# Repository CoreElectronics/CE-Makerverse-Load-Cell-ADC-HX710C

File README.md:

# Makerverse™ Load Cell ADC

This is the repo for the Core Electronics [Makerverse Load Cell ADC](https://core-electronics.com.au/catalog/product/view/sku/ce08248).

The PCB layout project requires KiCAD 6.0 or newer to view. The schematic is provided in PDF format in the Documents folder.

## License
This project is open source - please review the LICENSE.md file for further licensing information.

If you have any technical questions, or concerns about licensing, please contact technical support on the [Core Electronics forums](https://forum.core-electronics.com.au/).

*\"Makerverse\" and the Makerverse logo are trademarks of Core Electronics Pty Ltd.*

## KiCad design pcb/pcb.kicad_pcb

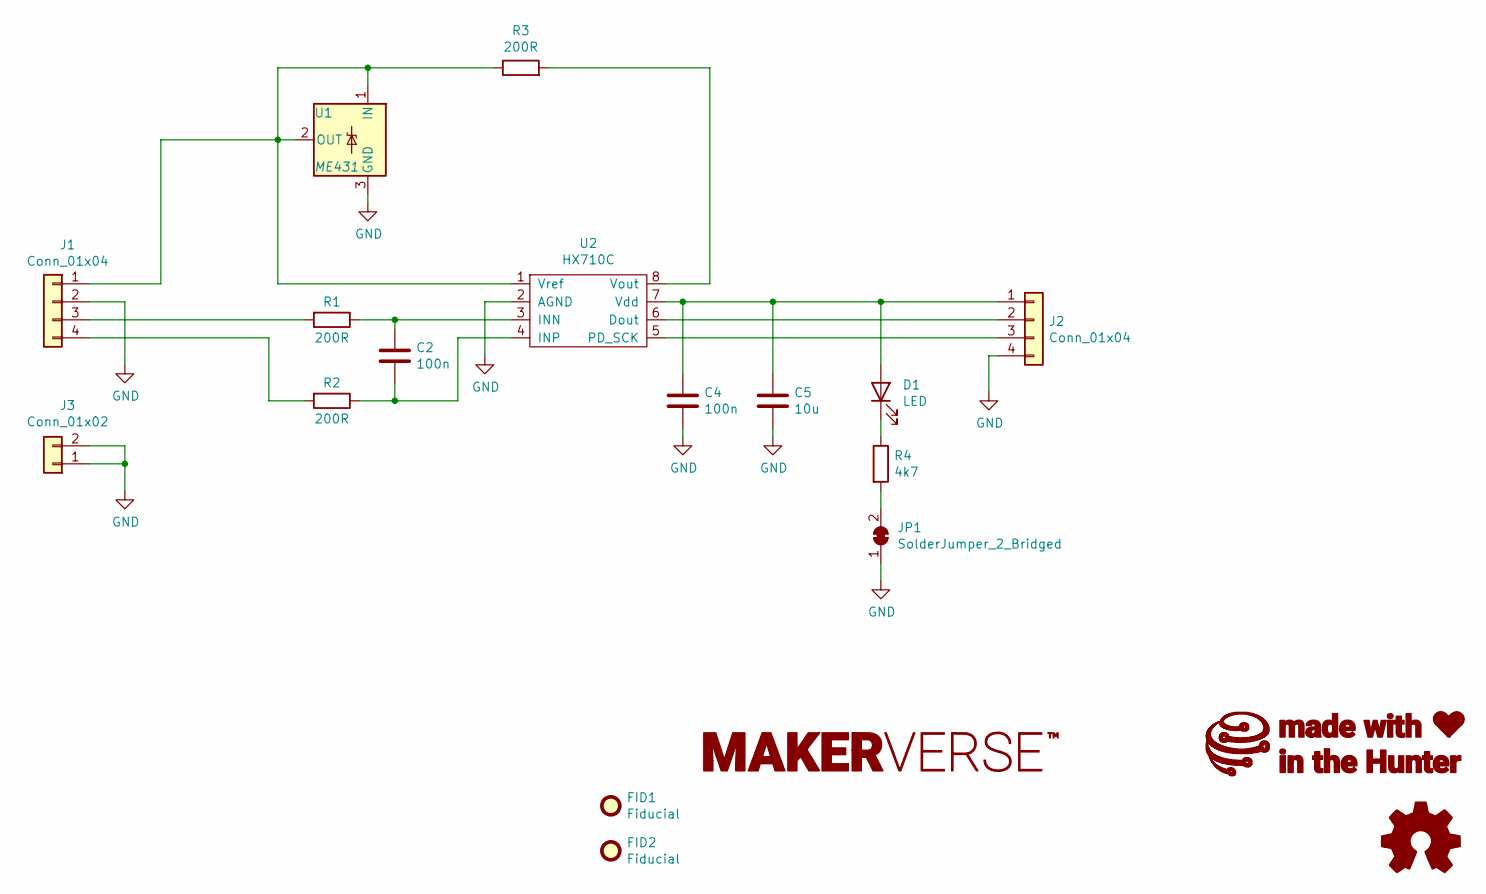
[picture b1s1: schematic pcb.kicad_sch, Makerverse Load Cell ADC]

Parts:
C2, C4: 100n; C_0402_1005Metric
C5: 10u; C_0603_1608Metric
D1: LED; LED_0603_1608Metric
FID1, FID2: Fiducial; Fiducial_1mm_Mask2mm
G1: LOGO_Makerverse; makerverse_logo_short_14.0x2.4mm
G2: LOGO_CoreElectronics_made-with-love; CE08248
J1: Conn_01x04; 2.54mm_screw_terminal-4-pin-left-entry
J2: Conn_01x04; 2.54mm_screw_terminal-4-pin-right-entry
J3: Conn_01x02; PinHeader_2x01_P2.54mm_Vertical
JP1: SolderJumper_2_Bridged; SolderJumper-2_P1.3mm_Bridged_RoundedPad1.0x1.5mm
LOGO1: Logo_Open_Hardware_Small; oshw_3.9x3.5mm
R1, R2, R3: 200R; R_0402_1005Metric
R4: 4k7; R_0402_1005Metric
U1: ME431; SOT-23
U2: HX710C; SOP-8_3.9x4.9mm_P1.27mm

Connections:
GND: C4.2, C5.2, J1.2, J2.4, J3.1, J3.2, JP1.1 (A), U1.3 (GND), U2.2 (AGND)
unnamed: C2.1, R1.1, U2.3 (INN)
unnamed: C2.2, R2.1, U2.4 (INP)
unnamed: C4.1, C5.1, D1.2 (A), J2.1, U2.7 (Vdd)
unnamed: D1.1 (K), R4.1
unnamed: J1.1, R3.1, U1.1 (IN), U1.2 (OUT), U2.1 (Vref)
unnamed: J1.3, R1.2
unnamed: J1.4, R2.2
unnamed: J2.2, U2.6 (Dout)
unnamed: J2.3, U2.5 (PD_SCK)
unnamed: JP1.2 (B), R4.2
unnamed: R3.2, U2.8 (Vout)

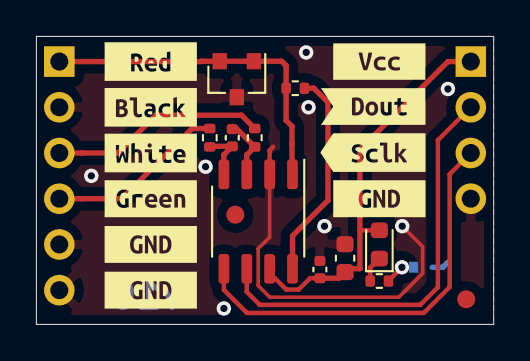
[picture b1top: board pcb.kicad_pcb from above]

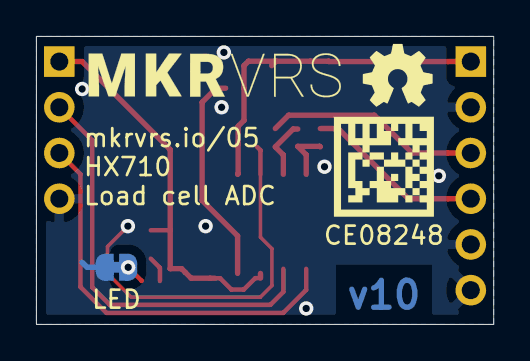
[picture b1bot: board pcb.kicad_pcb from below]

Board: 2 copper layers, 25.4 x 16.0 mm, 29 parts (4 on the bottom side), 12 nets.

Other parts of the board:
kibuzzard-619C2EB0, kibuzzard-619C2EB0#2, kibuzzard-6189F0B9, kibuzzard-6189F00D, kibuzzard-6189F003, kibuzzard-6189F021, kibuzzard-6189F029, kibuzzard-6189F085, kibuzzard-6189FDB3, kibuzzard-6189FDF6: G***; label

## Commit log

2022-06-14 Typo fix

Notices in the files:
pcb/pcb.kicad_sch:
License: CCASAv4.0 https://creativecommons.org/licenses/by-sa/4.0
